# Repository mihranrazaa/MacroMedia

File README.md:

# MacroMedia(HackPad)

## Introduction

Hello viewers this project was created by watching and learning how to make a macropad by [Hackpad](https://hackpad.hackclub.com/) , An event organised by [Hackclub](https://hackclub.com/). With the teachings i created **MacroMedia** which controls all your media with just one click, based on XIAO RP2040 MCU. Enjoy :)

## Extra Stuff

### Gratitude
- Thanks to Hackclub and Hackpad for making me do this brilliant project, More coming :).
- Thanks to my potato for helping me till the end.
- Thanks to myself for completing the project and not getting distracted with another project.
- And Thank you for Reading?

### Challenges
Never thought i would rage quite while i'm building something interesting, my potato(Yeah that's the name of my laptop) was like a heater when i was using CAD Software, i literally tried 5 software checking which worked the smoothest and none worked then shifted too browser based onshape tool which at the end atleast worked properly. Time to change my potato 😂

---
## Inner-Workings

### Specifications
####  BOM
- 1x XIAO RP2040
- 1x 0.91 inch OLED displays
- 8x Through-hole 1N4148 Diodes
- 8x Blank DSA keycaps
- 1x EC11 Rotary encoders
- 8x MX-Style switches
- 4x M3x16 Bolt
- 4x M3 Heatset

#### Others
- KMK Firmware
- Plate.stl
- Body.stl

---
## Images

### Schematics and PCB Design

---

---
### 3D Printed Case
Plate:

---

Body :

---

Both :

**I wasn't able to merge them together my potato laptop was already lagging too much and taking away all my time. Hope you understand. Dimensions have been checked.**
(If need a video of me building this 3D model you ask me, it's quite funny lol. )

Combined:

(Fixed the issue...)

---

BYEEEEE
Check my [Blog](https://mihranrazaa.pages.dev/) 
~ mihranrazaa

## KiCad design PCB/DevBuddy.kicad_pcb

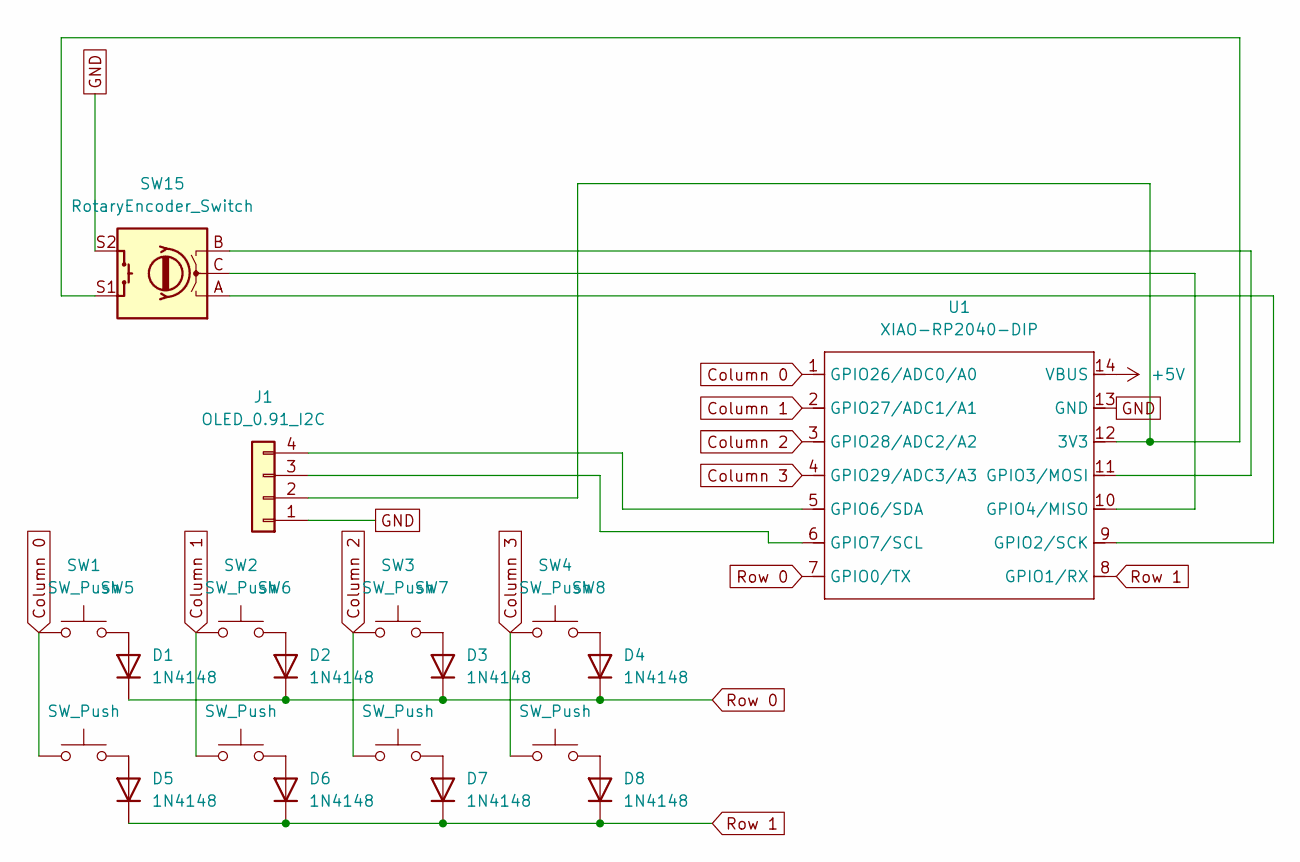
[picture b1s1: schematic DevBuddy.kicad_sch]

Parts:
D1, D2, D3, D4, D5, D6, D7, D8: 1N4148; D_DO-35_SOD27_P7.62mm_Horizontal
J1: OLED_0.91_I2C; SSD1306-0.91-OLED-4pin-128x32
SW1, SW2, SW3, SW4, SW5, SW6, SW7, SW8: SW_Push; SW_Cherry_MX_1.00u_PCB
SW15: RotaryEncoder_Switch; RotaryEncoder_Alps_EC11E-Switch_Vertical_H20mm
U1: XIAO-RP2040-DIP

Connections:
+5V: U1.14 (VBUS)
Column 0: SW1.1, SW5.1, U1.1 (GPIO26/ADC0/A0)
Column 1: SW2.1, SW6.1, U1.2 (GPIO27/ADC1/A1)
Column 2: SW3.1, SW7.1, U1.3 (GPIO28/ADC2/A2)
Column 3: SW4.1, SW8.1, U1.4 (GPIO29/ADC3/A3)
GND: J1.1 (GND), SW15.S2, U1.13 (GND)
unnamed: D1.2 (A), SW1.2
unnamed: D2.2 (A), SW2.2
unnamed: D3.2 (A), SW3.2
unnamed: D4.2 (A), SW4.2
unnamed: D5.2 (A), SW5.2
unnamed: D6.2 (A), SW6.2
unnamed: D7.2 (A), SW7.2
unnamed: D8.2 (A), SW8.2
unnamed: J1.3 (SCL), U1.6 (GPIO7/SCL)
unnamed: J1.4 (SDA), U1.5 (GPIO6/SDA)
unnamed: J1.2 (VCC), SW15.S1, U1.12 (3V3)
unnamed: SW15.A, U1.9 (GPIO2/SCK)
unnamed: SW15.B, U1.11 (GPIO3/MOSI)
unnamed: SW15.C, U1.10 (GPIO4/MISO)
Row 0: D1.1 (K), D2.1 (K), D3.1 (K), D4.1 (K), U1.7 (GPIO0/TX)
Row 1: D5.1 (K), D6.1 (K), D7.1 (K), D8.1 (K), U1.8 (GPIO1/RX)

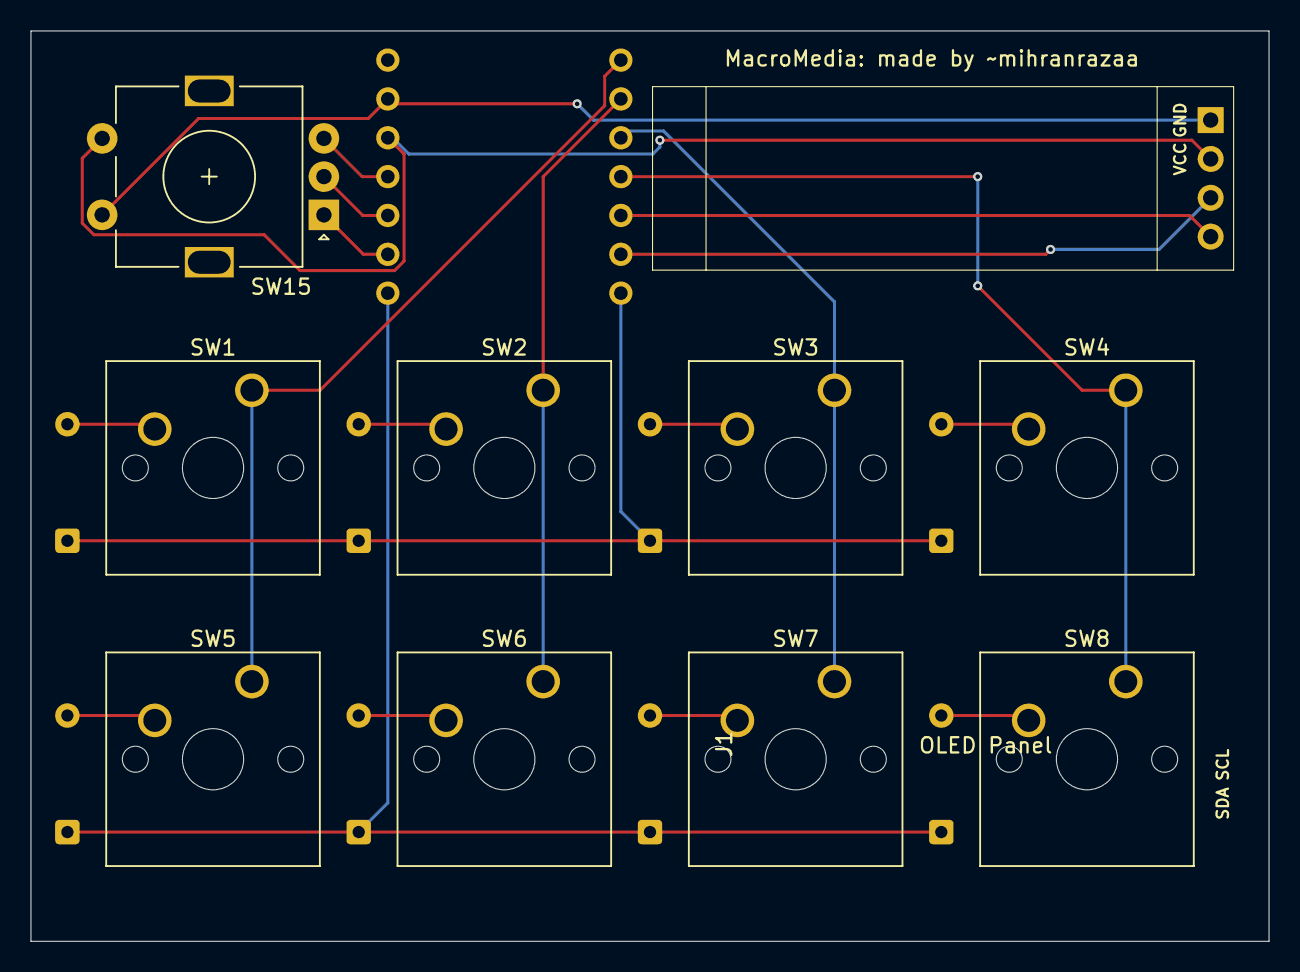
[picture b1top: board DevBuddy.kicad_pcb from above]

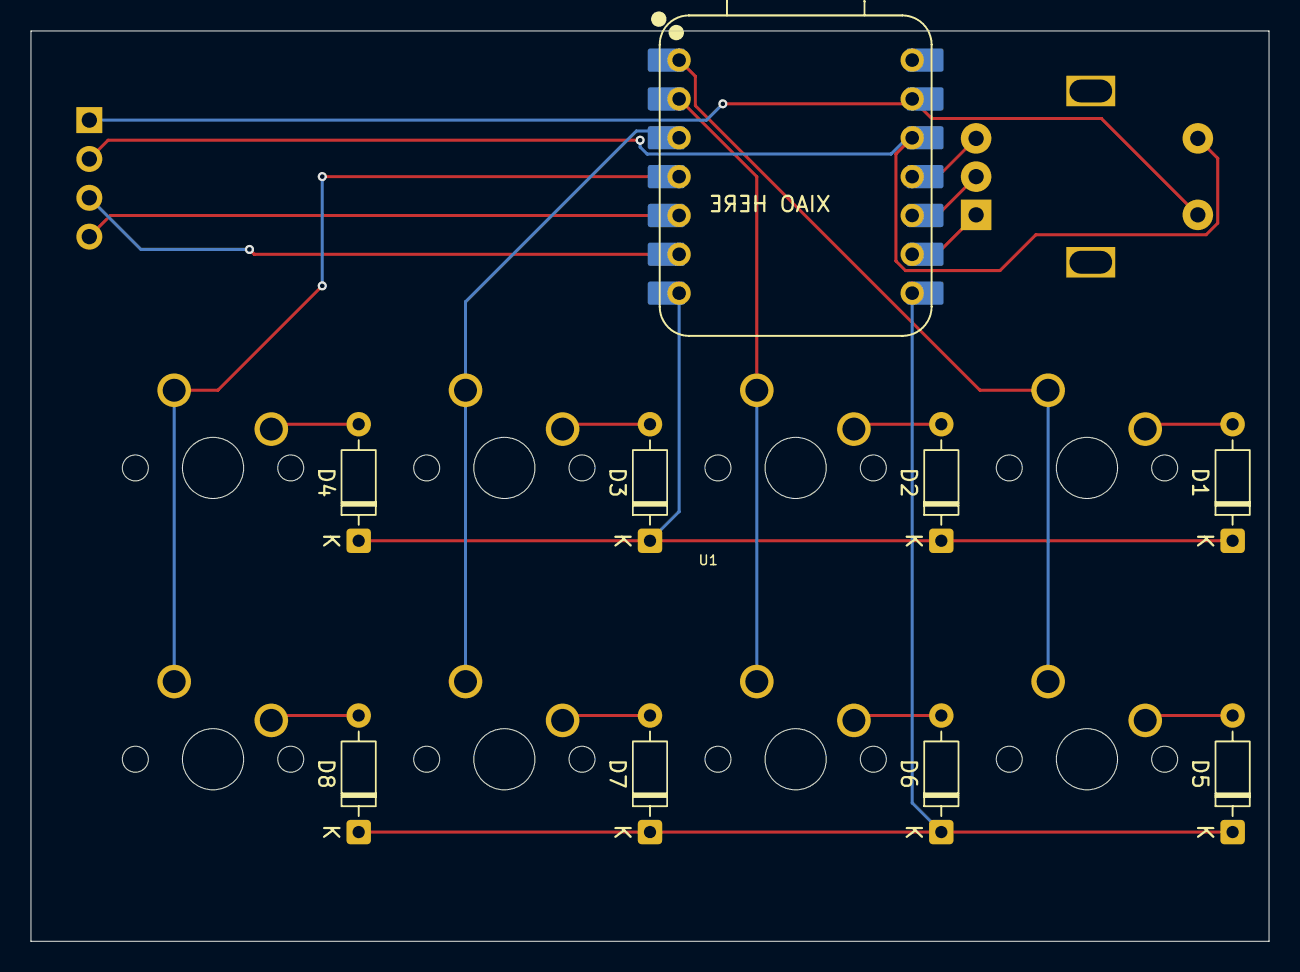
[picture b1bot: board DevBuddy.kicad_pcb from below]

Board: 2 copper layers, 81.0 x 59.5 mm, 19 parts (9 on the bottom side), 21 nets.

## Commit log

2025-06-10 update initial V1
2025-06-11 first release
2025-06-11 Fix images not showing
2025-06-12 fix spelling and update readme
